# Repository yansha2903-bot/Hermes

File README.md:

# HERMES 🚀

## Project Overview
The goal of this project was to design an hardware board integrated with an IMU sensor and program it using low-level I2C register configuration.

### Hardware Details
* **Microcontroller:** Seeed Studio XIAO RP2040
* **Sensor:** MPU-6050 Accelerometer & Gyroscope
* **Components:** 0402 SMD resistors and filtering/decoupling capacitors (2.2nF for CPOUT, 100nF for REGOUT, and 0.1uF bypass caps)
* **Bus:** I2C interface pulled up via 4.7kΩ resistors on a single top copper layer (`F.Cu`).

### Firmware Details
* Written in **Arduino C++** using the built-in `Wire.h` library.
* Directly reads and configures registers (`0x6B` for sensor power boot-up and `0x1B` for gyroscope scaling).
* Implements sequential reading starting from register `0x43` using bit-shifting (`<< 8`) to turn 8-bit pieces into real 16-bit data.
* Calculates cumulative angular rotation (`rotationZ`) dynamically using time intervals (`dt`).

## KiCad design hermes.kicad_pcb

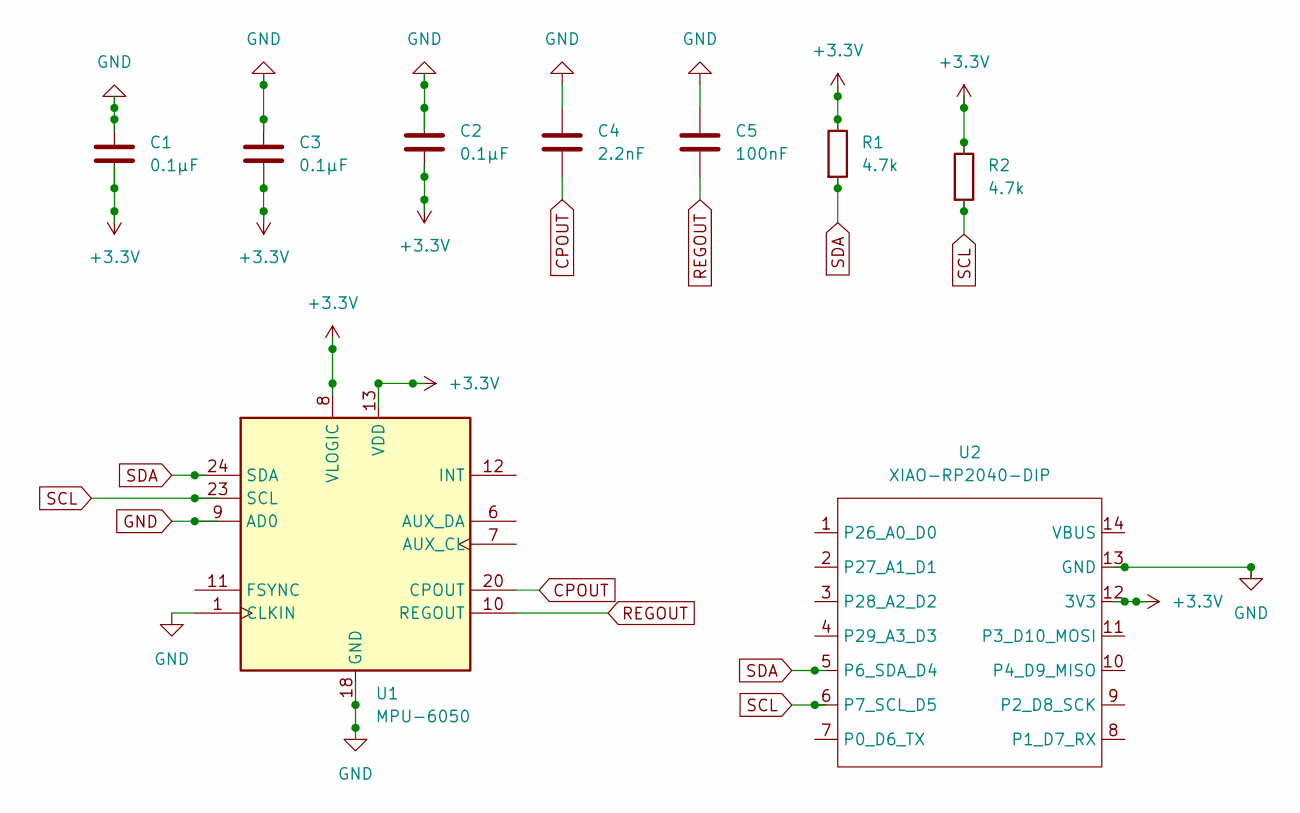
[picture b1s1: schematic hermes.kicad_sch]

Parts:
C1, C2, C3: 0.1µF; C_0402_1005Metric
C4: 2.2nF; C_0402_1005Metric
C5: 100nF; C_0402_1005Metric
R1, R2: 4.7k; R_0402_1005Metric
U1: MPU-6050; InvenSense_QFN-24_4x4mm_P0.5mm
U2: XIAO-RP2040-DIP

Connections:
+3.3V: C1.2, C2.2, C3.2, R1.1, R2.1, U1.8 (VLOGIC), U1.13 (VDD), U2.12 (3V3)
CPOUT: C4.2, U1.20 (CPOUT)
GND: C1.1, C2.1, C3.1, C4.1, C5.1, U1.1 (CLKIN), U1.9 (AD0), U1.18 (GND), U2.13 (GND)
REGOUT: C5.2, U1.10 (REGOUT)
SCL: R2.2, U1.23 (SCL), U2.6 (P7_SCL_D5)
SDA: R1.2, U1.24 (SDA), U2.5 (P6_SDA_D4)

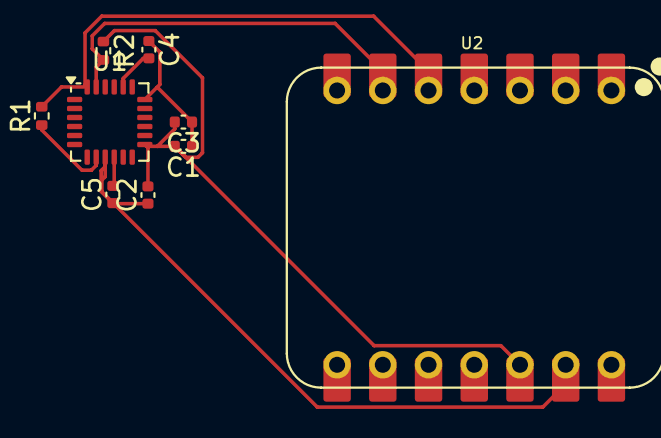
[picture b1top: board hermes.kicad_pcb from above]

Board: 2 copper layers, 9 parts (0 on the bottom side), 6 nets.

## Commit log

2026-06-17 Create LICENSE
